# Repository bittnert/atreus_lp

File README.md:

# Atreus Low Profile Keyboard

This repository contains the files for a low profile variant of the atreus keyboard. THe original atreus keyboard can be found [[https://gitlab.com/technomancy/atreus][here]].

** The low profile atreus keyboard is still under development. The first PCB version has been ordered but not build or tested yet. **

The Keyboard uses Kailh Choc key switches which are soldered into a PCB. An addressable LED can be added to each key switch. Due to the size constraints, only 2020 LEDs (or smaller) can be used.

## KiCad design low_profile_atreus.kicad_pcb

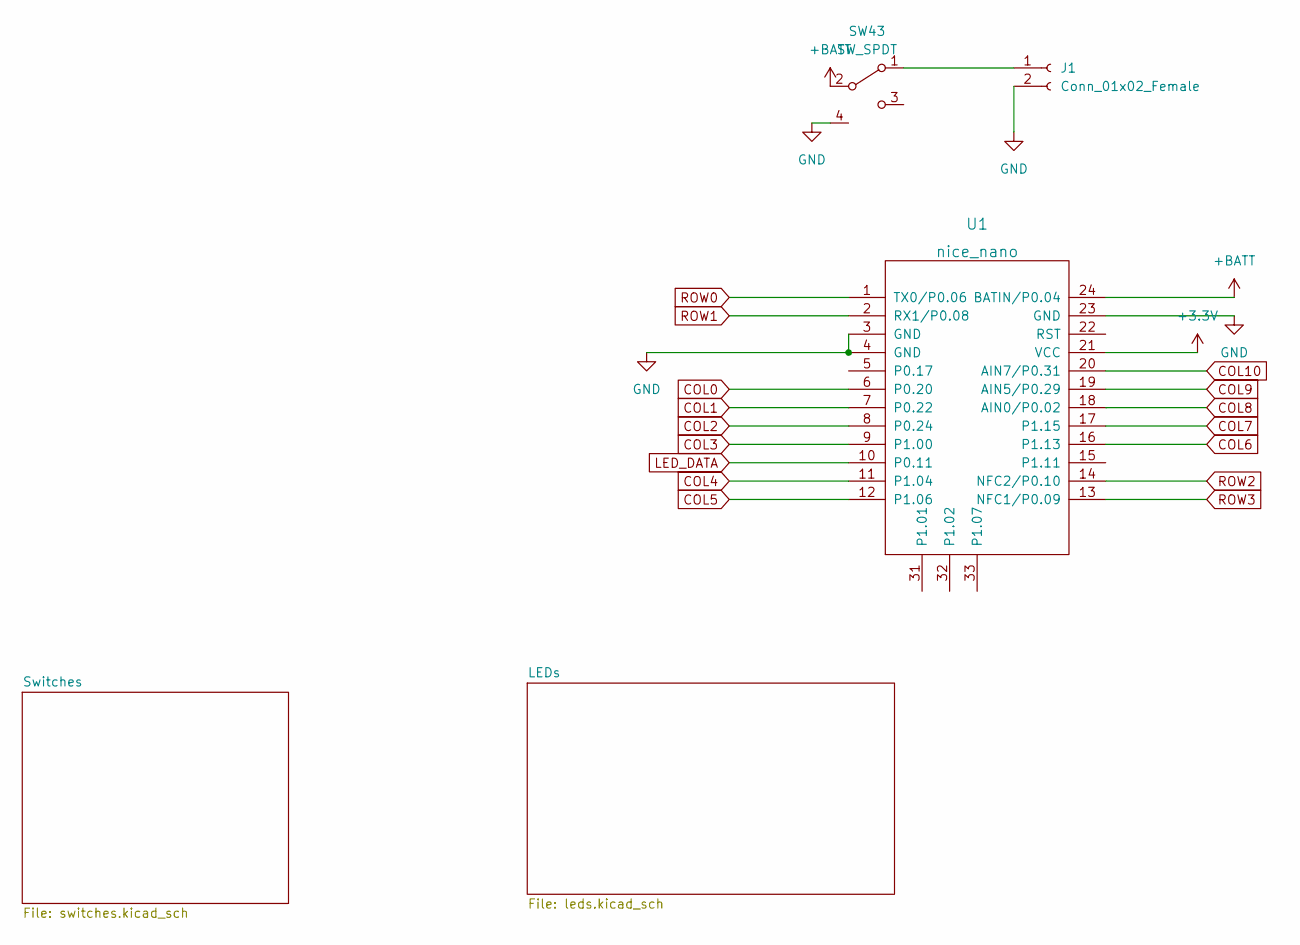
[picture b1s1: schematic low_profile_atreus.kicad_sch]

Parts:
J1: Conn_01x02_Female; JST_PH_S2B-PH-K_1x02_P2.00mm_Horizontal
SW43: SW_SPDT; MSK12C02
U1: nice_nano

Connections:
+3V3: U1.21 (VCC); also elsewhere on the board
+BATT: SW43.2 (B), U1.24 (BATIN/P0.04)
COL0: U1.6 (P0.20); also elsewhere on the board
COL1: U1.7 (P0.22); also elsewhere on the board
COL2: U1.8 (P0.24); also elsewhere on the board
COL3: U1.9 (P1.00); also elsewhere on the board
COL4: U1.11 (P1.04); also elsewhere on the board
COL5: U1.12 (P1.06); also elsewhere on the board
COL6: U1.16 (P1.13); also elsewhere on the board
COL7: U1.17 (P1.15); also elsewhere on the board
COL8: U1.18 (AIN0/P0.02); also elsewhere on the board
COL9: U1.19 (AIN5/P0.29); also elsewhere on the board
COL10: U1.20 (AIN7/P0.31); also elsewhere on the board
GND: J1.2, SW43.4 (GND), U1.3 (GND), U1.4 (GND), U1.23 (GND); also elsewhere on the board
LED_DATA: U1.10 (P0.11); also elsewhere on the board
unnamed: J1.1, SW43.1 (A)
ROW0: U1.1 (TX0/P0.06); also elsewhere on the board
ROW1: U1.2 (RX1/P0.08); also elsewhere on the board
ROW2: U1.14 (NFC2/P0.10); also elsewhere on the board
ROW3: U1.13 (NFC1/P0.09); also elsewhere on the board

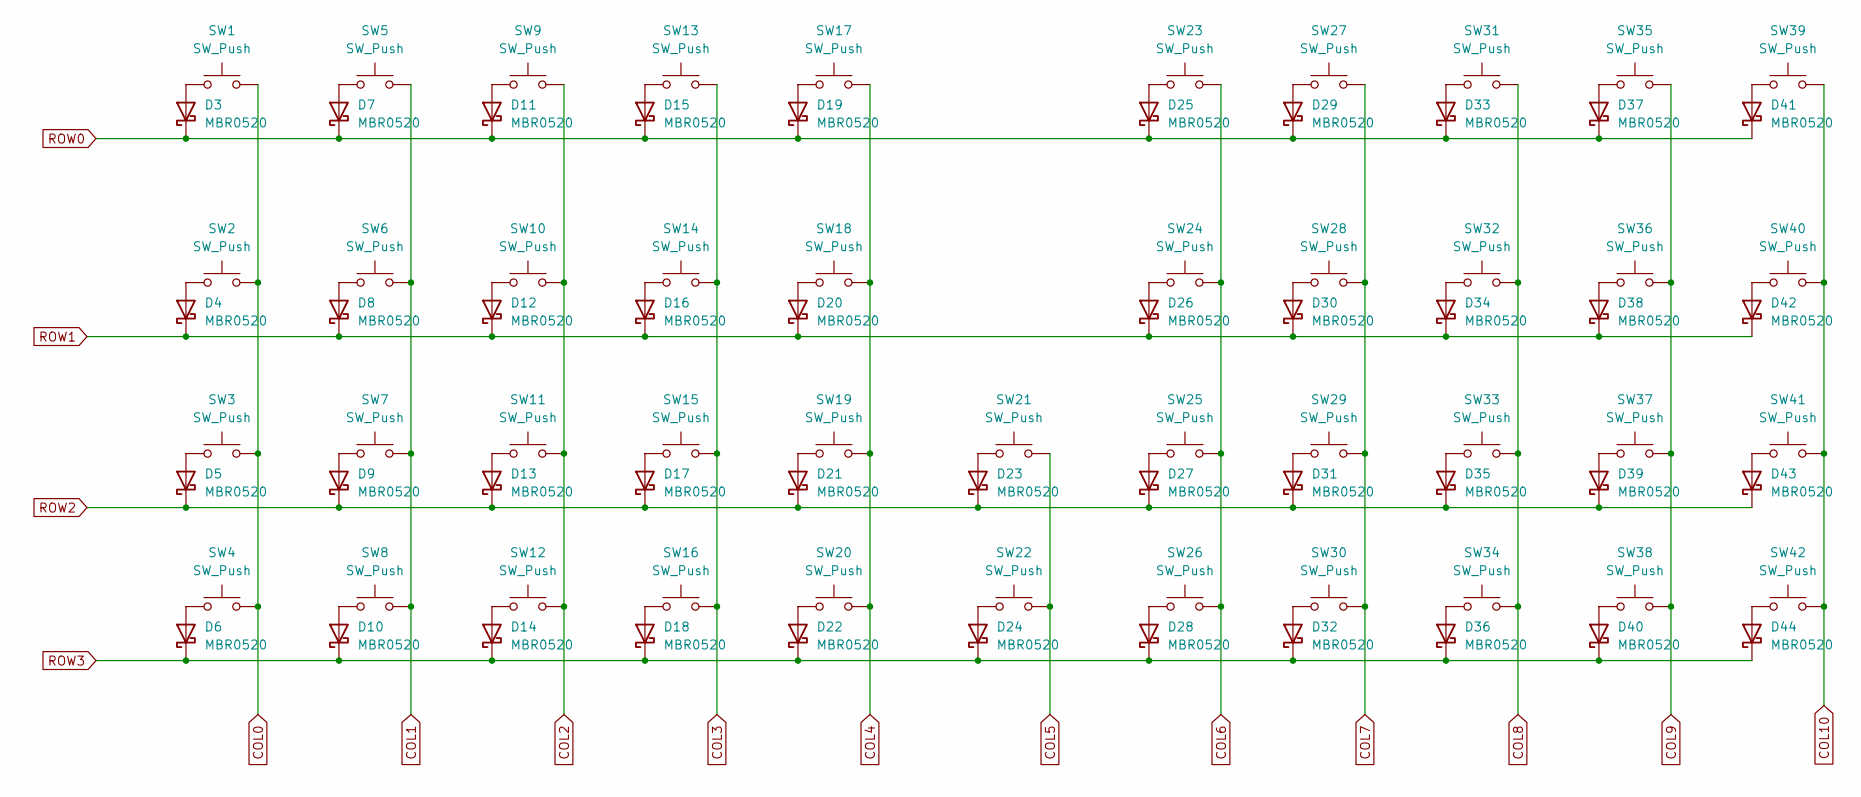
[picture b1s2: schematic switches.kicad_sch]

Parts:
D3, D4, D5, D6, D7, D8, D9, D10, D11, D12, D13, D14, D15, D16, D17, D18, D19, D20, D21, D22, D23, D24, D25, D26, D27, D28, D29, D30, D31, D32, D33, D34, D35, D36, D37, D38, D39, D40, D41, D42, D43, D44: MBR0520; D_SOD-123
SW1, SW2, SW3, SW4, SW5, SW6, SW7, SW8, SW9, SW10, SW11, SW12, SW13, SW14, SW15, SW16, SW17, SW18, SW19, SW20, SW21, SW22, SW23, SW24, SW25, SW26, SW27, SW28, SW29, SW30, SW31, SW32, SW33, SW34, SW35, SW36, SW37, SW38, SW39, SW40, SW41, SW42: SW_Push; SW_PG1350

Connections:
COL0: SW1.2, SW2.2, SW3.2, SW4.2; also elsewhere on the board
COL1: SW5.2, SW6.2, SW7.2, SW8.2; also elsewhere on the board
COL2: SW9.2, SW10.2, SW11.2, SW12.2; also elsewhere on the board
COL3: SW13.2, SW14.2, SW15.2, SW16.2; also elsewhere on the board
COL4: SW17.2, SW18.2, SW19.2, SW20.2; also elsewhere on the board
COL5: SW21.2, SW22.2; also elsewhere on the board
COL6: SW23.2, SW24.2, SW25.2, SW26.2; also elsewhere on the board
COL7: SW27.2, SW28.2, SW29.2, SW30.2; also elsewhere on the board
COL8: SW31.2, SW32.2, SW33.2, SW34.2; also elsewhere on the board
COL9: SW35.2, SW36.2, SW37.2, SW38.2; also elsewhere on the board
COL10: SW39.2, SW40.2, SW41.2, SW42.2; also elsewhere on the board
unnamed: D3.2 (A), SW1.1
unnamed: D4.2 (A), SW2.1
unnamed: D5.2 (A), SW3.1
unnamed: D6.2 (A), SW4.1
unnamed: D7.2 (A), SW5.1
unnamed: D8.2 (A), SW6.1
unnamed: D9.2 (A), SW7.1
unnamed: D10.2 (A), SW8.1
unnamed: D11.2 (A), SW9.1
unnamed: D12.2 (A), SW10.1
unnamed: D13.2 (A), SW11.1
unnamed: D14.2 (A), SW12.1
unnamed: D15.2 (A), SW13.1
unnamed: D16.2 (A), SW14.1
unnamed: D17.2 (A), SW15.1
unnamed: D18.2 (A), SW16.1
unnamed: D19.2 (A), SW17.1
unnamed: D20.2 (A), SW18.1
unnamed: D21.2 (A), SW19.1
unnamed: D22.2 (A), SW20.1
unnamed: D23.2 (A), SW21.1
unnamed: D24.2 (A), SW22.1
unnamed: D25.2 (A), SW23.1
unnamed: D26.2 (A), SW24.1
unnamed: D27.2 (A), SW25.1
unnamed: D28.2 (A), SW26.1
unnamed: D29.2 (A), SW27.1
unnamed: D30.2 (A), SW28.1
unnamed: D31.2 (A), SW29.1
unnamed: D32.2 (A), SW30.1
unnamed: D33.2 (A), SW31.1
unnamed: D34.2 (A), SW32.1
unnamed: D35.2 (A), SW33.1
unnamed: D36.2 (A), SW34.1
unnamed: D37.2 (A), SW35.1
unnamed: D38.2 (A), SW36.1
unnamed: D39.2 (A), SW37.1
unnamed: D40.2 (A), SW38.1
unnamed: D41.2 (A), SW39.1
unnamed: D42.2 (A), SW40.1
unnamed: D43.2 (A), SW41.1
unnamed: D44.2 (A), SW42.1
ROW0: D3.1 (K), D7.1 (K), D11.1 (K), D15.1 (K), D19.1 (K), D25.1 (K), D29.1 (K), D33.1 (K), D37.1 (K), D41.1 (K); also elsewhere on the board
ROW1: D4.1 (K), D8.1 (K), D12.1 (K), D16.1 (K), D20.1 (K), D26.1 (K), D30.1 (K), D34.1 (K), D38.1 (K), D42.1 (K); also elsewhere on the board
ROW2: D5.1 (K), D9.1 (K), D13.1 (K), D17.1 (K), D21.1 (K), D23.1 (K), D27.1 (K), D31.1 (K), D35.1 (K), D39.1 (K), D43.1 (K); also elsewhere on the board
ROW3: D6.1 (K), D10.1 (K), D14.1 (K), D18.1 (K), D22.1 (K), D24.1 (K), D28.1 (K), D32.1 (K), D36.1 (K), D40.1 (K), D44.1 (K); also elsewhere on the board

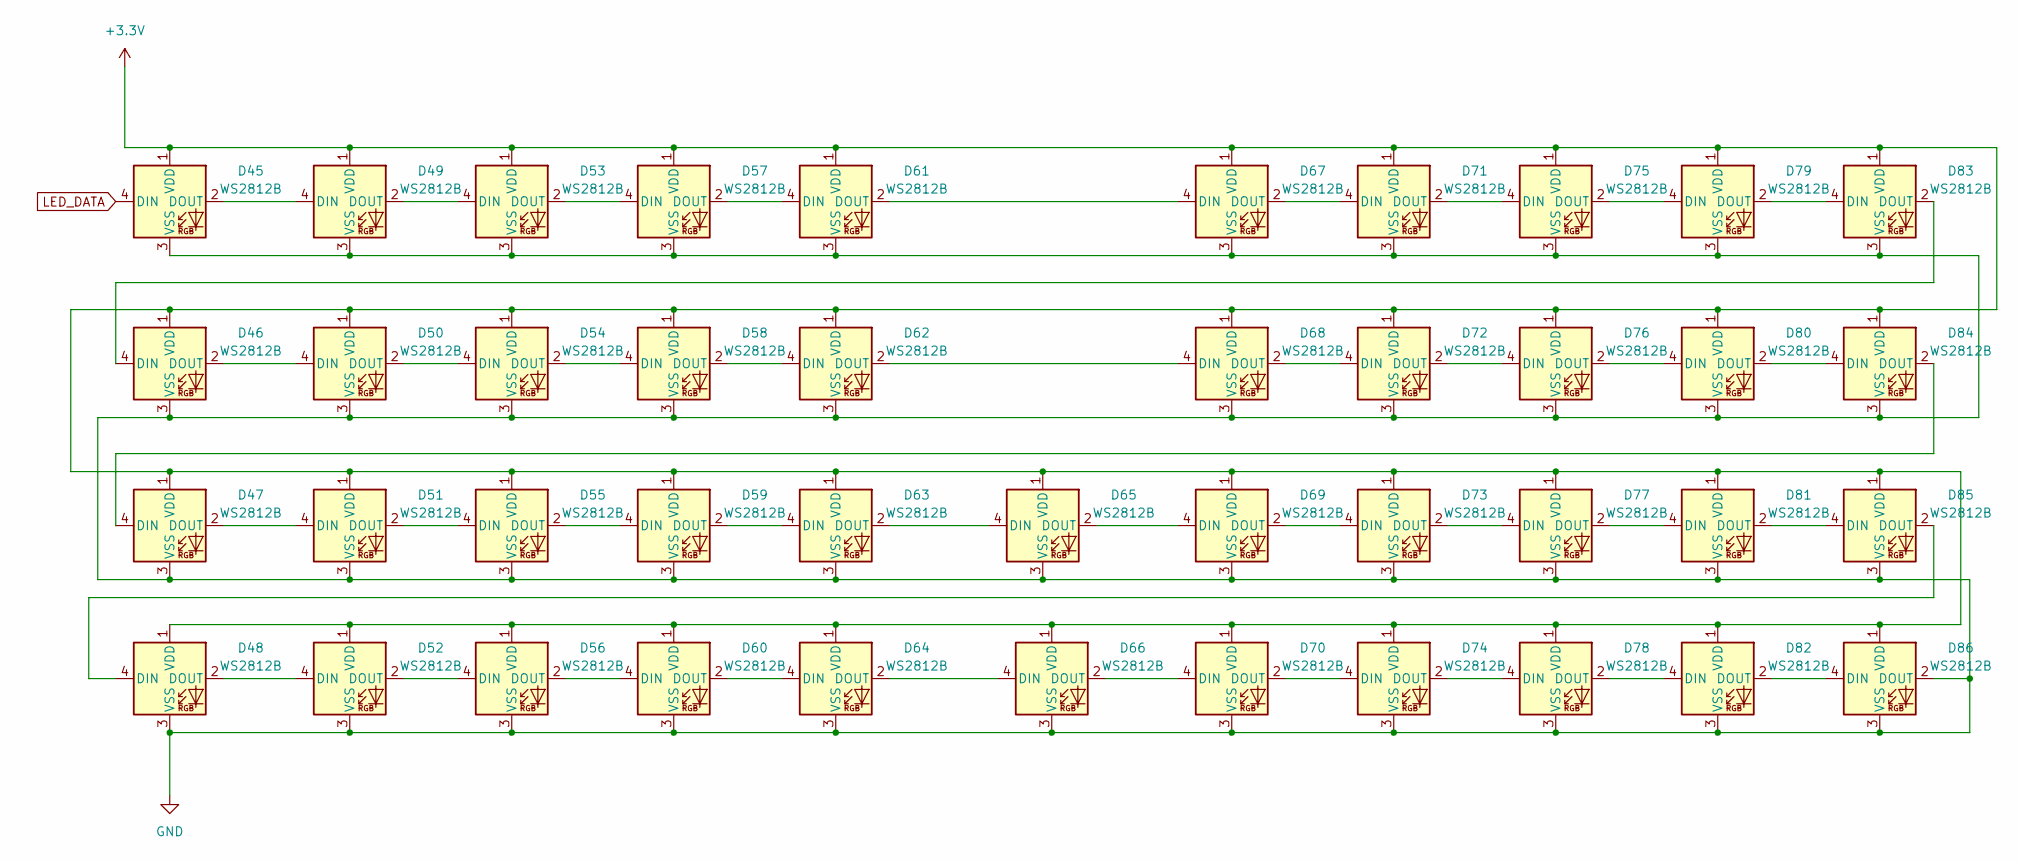
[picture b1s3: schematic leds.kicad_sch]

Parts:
D45, D46, D47, D48, D49, D50, D51, D52, D53, D54, D55, D56, D57, D58, D59, D60, D61, D62, D63, D64, D65, D66, D67, D68, D69, D70, D71, D72, D73, D74, D75, D76, D77, D78, D79, D80, D81, D82, D83, D84, D85, D86: WS2812B; LED_Cree-PLCC4_2x2mm_CW

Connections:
+3V3: D45.1 (VDD), D46.1 (VDD), D47.1 (VDD), D48.1 (VDD), D49.1 (VDD), D50.1 (VDD), D51.1 (VDD), D52.1 (VDD), D53.1 (VDD), D54.1 (VDD), D55.1 (VDD), D56.1 (VDD), D57.1 (VDD), D58.1 (VDD), D59.1 (VDD), D60.1 (VDD), D61.1 (VDD), D62.1 (VDD), D63.1 (VDD), D64.1 (VDD), D65.1 (VDD), D66.1 (VDD), D67.1 (VDD), D68.1 (VDD), D69.1 (VDD), D70.1 (VDD), D71.1 (VDD), D72.1 (VDD), D73.1 (VDD), D74.1 (VDD), D75.1 (VDD), D76.1 (VDD), D77.1 (VDD), D78.1 (VDD), D79.1 (VDD), D80.1 (VDD), D81.1 (VDD), D82.1 (VDD), D83.1 (VDD), D84.1 (VDD), D85.1 (VDD), D86.1 (VDD); also elsewhere on the board
GND: D45.3 (VSS), D46.3 (VSS), D47.3 (VSS), D48.3 (VSS), D49.3 (VSS), D50.3 (VSS), D51.3 (VSS), D52.3 (VSS), D53.3 (VSS), D54.3 (VSS), D55.3 (VSS), D56.3 (VSS), D57.3 (VSS), D58.3 (VSS), D59.3 (VSS), D60.3 (VSS), D61.3 (VSS), D62.3 (VSS), D63.3 (VSS), D64.3 (VSS), D65.3 (VSS), D66.3 (VSS), D67.3 (VSS), D68.3 (VSS), D69.3 (VSS), D70.3 (VSS), D71.3 (VSS), D72.3 (VSS), D73.3 (VSS), D74.3 (VSS), D75.3 (VSS), D76.3 (VSS), D77.3 (VSS), D78.3 (VSS), D79.3 (VSS), D80.3 (VSS), D81.3 (VSS), D82.3 (VSS), D83.3 (VSS), D84.3 (VSS), D85.3 (VSS), D86.2 (DOUT), D86.3 (VSS); also elsewhere on the board
LED_DATA: D45.4 (DIN); also elsewhere on the board
unnamed: D45.2 (DOUT), D49.4 (DIN)
unnamed: D46.2 (DOUT), D50.4 (DIN)
unnamed: D46.4 (DIN), D83.2 (DOUT)
unnamed: D47.2 (DOUT), D51.4 (DIN)
unnamed: D47.4 (DIN), D84.2 (DOUT)
unnamed: D48.2 (DOUT), D52.4 (DIN)
unnamed: D48.4 (DIN), D85.2 (DOUT)
unnamed: D49.2 (DOUT), D53.4 (DIN)
unnamed: D50.2 (DOUT), D54.4 (DIN)
unnamed: D51.2 (DOUT), D55.4 (DIN)
unnamed: D52.2 (DOUT), D56.4 (DIN)
unnamed: D53.2 (DOUT), D57.4 (DIN)
unnamed: D54.2 (DOUT), D58.4 (DIN)
unnamed: D55.2 (DOUT), D59.4 (DIN)
unnamed: D56.2 (DOUT), D60.4 (DIN)
unnamed: D57.2 (DOUT), D61.4 (DIN)
unnamed: D58.2 (DOUT), D62.4 (DIN)
unnamed: D59.2 (DOUT), D63.4 (DIN)
unnamed: D60.2 (DOUT), D64.4 (DIN)
unnamed: D61.2 (DOUT), D67.4 (DIN)
unnamed: D62.2 (DOUT), D68.4 (DIN)
unnamed: D63.2 (DOUT), D65.4 (DIN)
unnamed: D64.2 (DOUT), D66.4 (DIN)
unnamed: D65.2 (DOUT), D69.4 (DIN)
unnamed: D66.2 (DOUT), D70.4 (DIN)
unnamed: D67.2 (DOUT), D71.4 (DIN)
unnamed: D68.2 (DOUT), D72.4 (DIN)
unnamed: D69.2 (DOUT), D73.4 (DIN)
unnamed: D70.2 (DOUT), D74.4 (DIN)
unnamed: D71.2 (DOUT), D75.4 (DIN)
unnamed: D72.2 (DOUT), D76.4 (DIN)
unnamed: D73.2 (DOUT), D77.4 (DIN)
unnamed: D74.2 (DOUT), D78.4 (DIN)
unnamed: D75.2 (DOUT), D79.4 (DIN)
unnamed: D76.2 (DOUT), D80.4 (DIN)
unnamed: D77.2 (DOUT), D81.4 (DIN)
unnamed: D78.2 (DOUT), D82.4 (DIN)
unnamed: D79.2 (DOUT), D83.4 (DIN)
unnamed: D80.2 (DOUT), D84.4 (DIN)
unnamed: D81.2 (DOUT), D85.4 (DIN)
unnamed: D82.2 (DOUT), D86.4 (DIN)

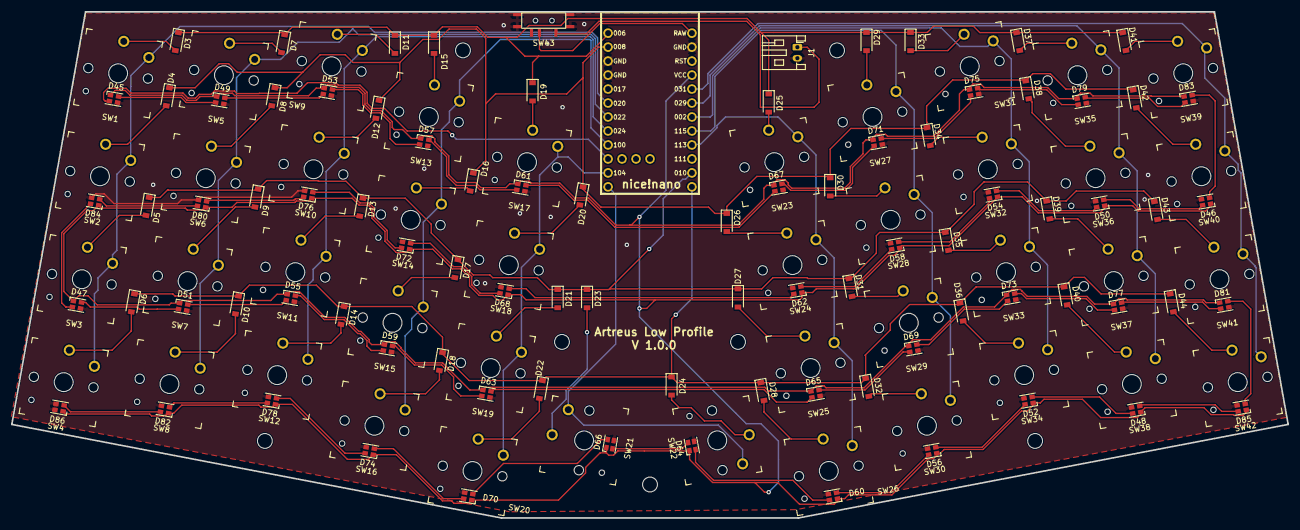
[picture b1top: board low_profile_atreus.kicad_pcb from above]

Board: 2 copper layers, 232.0 x 92.0 mm, 136 parts (0 on the bottom side), 103 nets.

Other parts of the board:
Mounting Hole 2, Mounting Hole 3, Mounting Hole 4, Mounting Hole 5, Mounting Hole 6, Mounting Hole 7: MountingHole_2.7mm_M2.5
mounting Hole 1: MountingHole_2.7mm_M2.5

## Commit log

2022-11-13 Atreus Low Profile PCB Version 1.0.0
